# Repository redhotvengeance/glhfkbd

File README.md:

# glhfkbd

A custom, split keyboard.

Features:
- Extremely minimalist design -- no bevels, no edges, just keys!
- Split body, for da ergonomics
- Row-staggered, for da muscle memory
- A "Y" and "B" key on both halves, for da bad typists
- Supports hotswap MX sockets
- Fully embedded electronics -- no dev boards!
- USB-C for the wired interconnect -- no live TRRS shorts!
- Either side can act as the host
- Driven by QMK firmware and fully customizable

## PCB

The PCB is all one unit, despite both halves of the keyboard being asymmetrical. Mouse bites are used to easily separate pieces. All gerbers are provided in this repo.

All electronics are embedded into the board itself. This eliminates the need for a dev board, but requires assembly by a PCB manufacturer. BOM and position files are provided in this repo.

## Case

All pieces for the case are provided as STEP files in this repo, with the exception of the switch plates, which are provided as PCB files so they can be manufactored in FR4.

### Switch plates (required)

Found in the `pcb` folder. Should be printed as non-copper and non-trace PCBs.

### Filler layer (optional)

3D printed layer that sites between the plates and PCBs (to fill the space between switches). Used for aesthetics and sound.

### Standoff layer (required)

Used to mount the PCBs and plates to the base. Can be easily 3D printed. Needs heat-set inserts added.

### Base (required)

Bottom of the keyboard. Can be 3D printed. Should have rubber feet added for stability.

As an upgrade, the base can be laser cut from metal. This adds weight, quality, and improved sound. I suggest using a ferrous metal (like carbon steel) so that each keyboard half can be easily attached to a magsafe stand for easy tenting.

## Sharing

Fully open source. Feel free to build it yourself.

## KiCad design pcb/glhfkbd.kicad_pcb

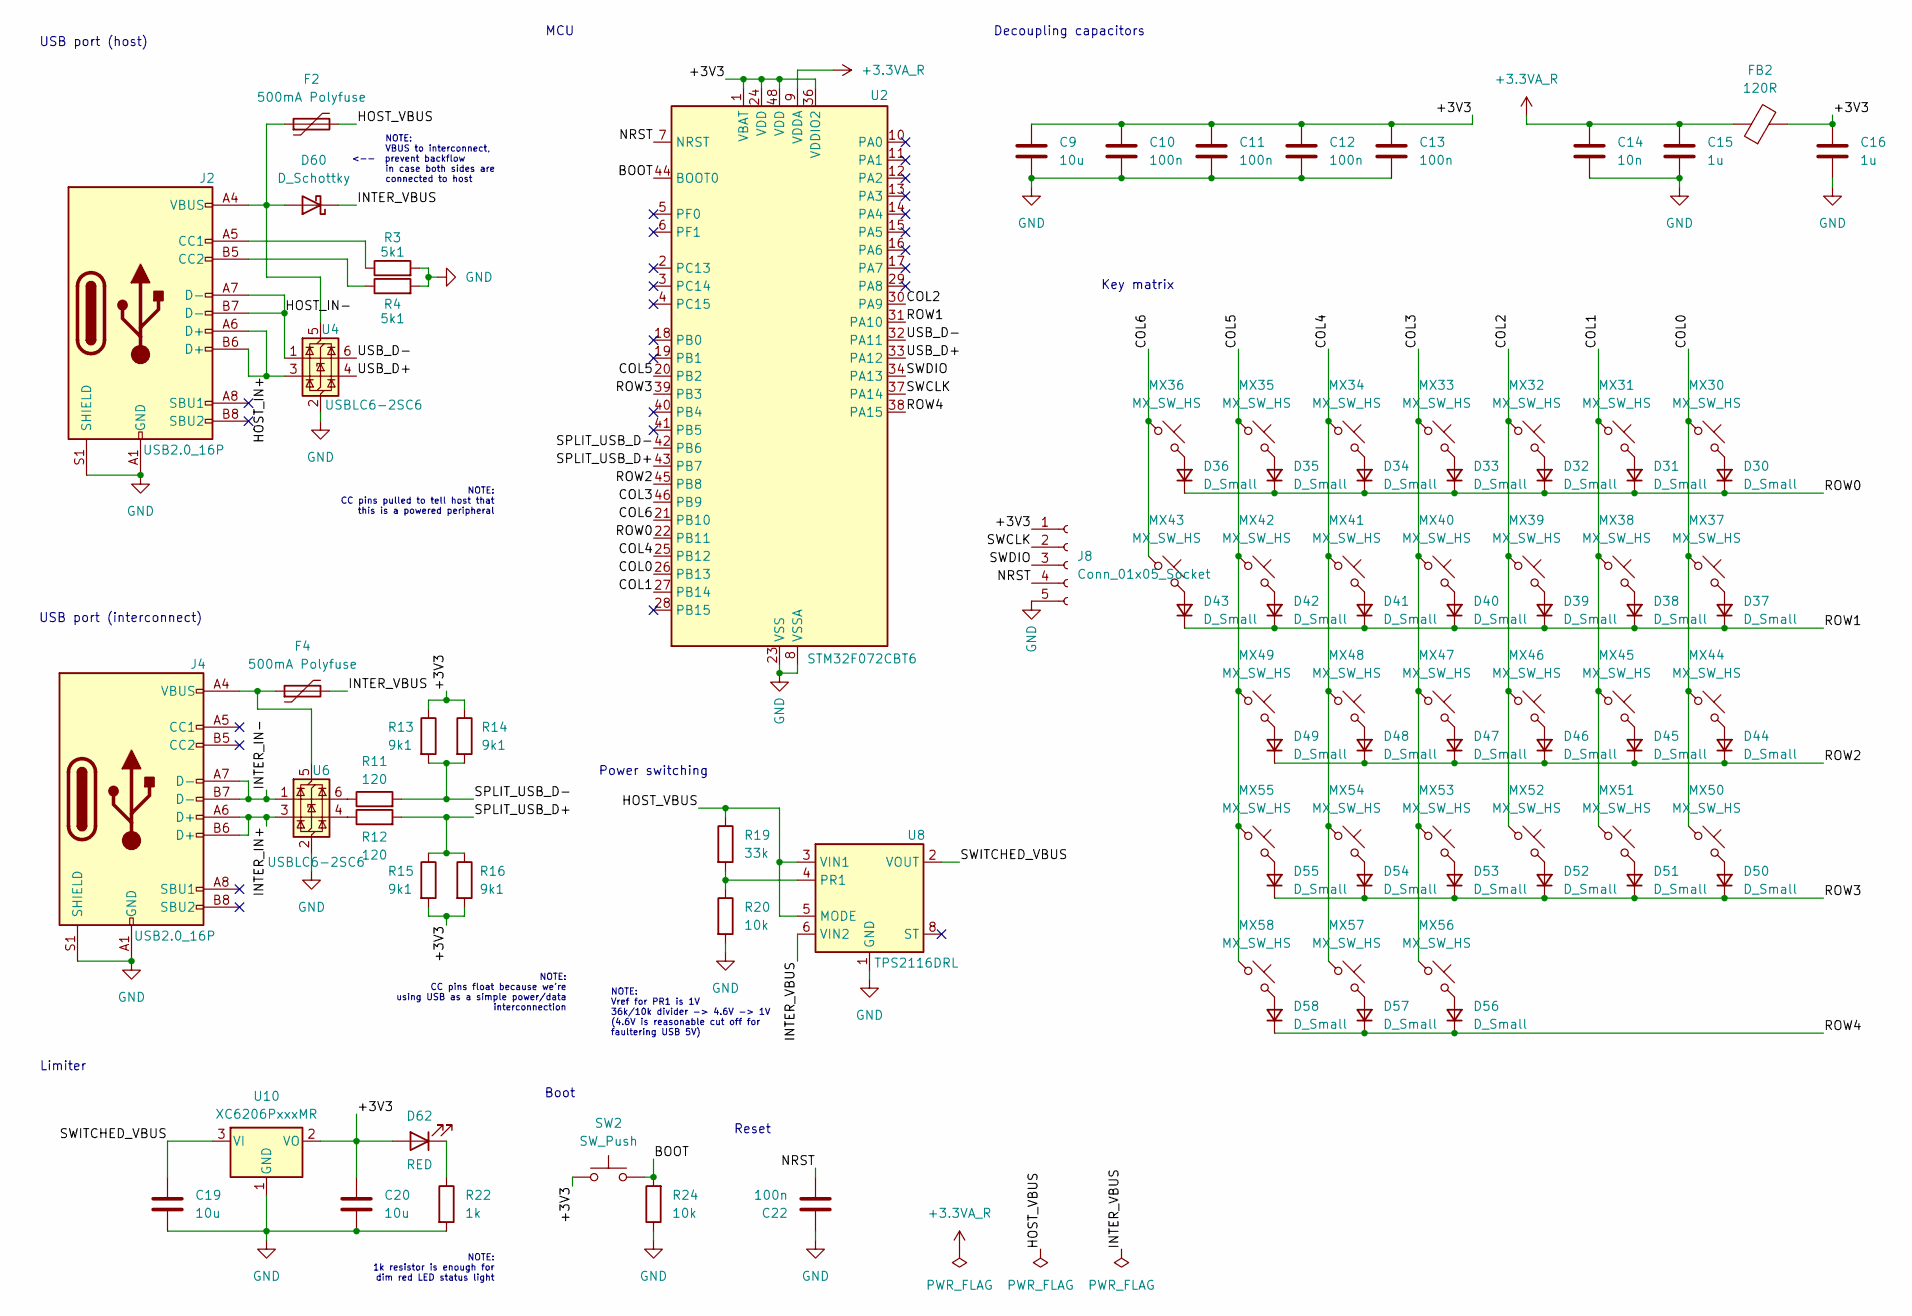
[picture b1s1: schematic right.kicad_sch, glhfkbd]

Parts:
C9, C19, C20: 10u; cap_10uf; Manufacturer Part CL05A106MQ5NUNC; LCSC C15525
C10, C11, C12, C13, C22: 100n; cap_100nf; Manufacturer Part CL05B104KB54PNC; LCSC C307331
C14: 10n; cap_10nf; Manufacturer Part CL05B103KB5NNNC; LCSC C15195
C15, C16: 1u; cap_1uf; Manufacturer Part CL05A105KA5NQNC; LCSC C52923
D30, D31, D32, D33, D34, D35, D36, D37, D38, D39, D40, D41, D42, D43, D44, D45, D46, D47, D48, D49, D50, D51, D52, D53, D54, D55, D56, D57, D58: D_Small; diode_sod123; Manufacturer Part 1N4148W; LCSC C81598
D60: D_Schottky; schottky; Manufacturer Part SS54; LCSC C22452
D62: RED; led; Manufacturer Part KT-0603R; LCSC C2286
F2, F4: 500mA Polyfuse; fuse_500ma; Manufacturer Part MF-FSMF050X-2; LCSC C210357
FB2: 120R; ferrite; Manufacturer Part BLM18SG260TN1D; LCSC C87063
J2, J4: USB2.0_16P; usb-c; Manufacturer Part TYPE-C-31-M-12; LCSC C165948
J8: Conn_01x05_Socket; PinHeader_1x05_P1.00mm_Vertical
MX30, MX31, MX32, MX33, MX34, MX35, MX36, MX37, MX38, MX39, MX40, MX41, MX42, MX43, MX44, MX45, MX46, MX47, MX48, MX49, MX50, MX51, MX52, MX53, MX54, MX55, MX56, MX57, MX58: MX_SW_HS; SW_MX_HS_CPG151101S11_1u
R3, R4: 5k1; res_5k1; Manufacturer Part 0402WGF5101TCE; LCSC C25905
R11, R12: 120; res_120; LCSC C25079
R13, R14, R15, R16: 9k1; res_9k1; LCSC C23260
R19: 33k; res_33k; Manufacturer Part 0402WGF3302TCE; LCSC C25779
R20, R24: 10k; res_10k; Manufacturer Part 0402WGF1002TCE; LCSC C25744
R22: 1k; res_1k; Manufacturer Part 0402WGF1001TCE; LCSC C11702
SW2: SW_Push; switch; Manufacturer Part TS-1088-AR02016; LCSC C720477
U2: STM32F072CBT6; stm32; Manufacturer Part STM32F072CBT6; LCSC C81720
U4, U6: USBLC6-2SC6; usblc6-2sc6; Manufacturer Part USBLC6-2SC6; LCSC C2827654
U8: TPS2116DRL; tps2116drlr; Manufacturer Part TPS2116DRLR; LCSC C3235557
U10: XC6206PxxxMR; xc6206; Manufacturer Part XC6206P332MR-G; LCSC C5446

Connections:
+3.3VA_R: C14.1, C15.1, FB2.1, U2.9 (VDDA)
/right/+3V3: C9.1, C10.1, C11.1, C12.1, C13.1, C16.1, C20.1, D62.2 (A), FB2.2, J8.1, R13.1, R14.1, R15.2, R16.2, SW2.1, U2.1 (VBAT), U2.24 (VDD), U2.36 (VDDIO2), U2.48 (VDD), U10.2 (VO)
/right/BOOT: R24.2, SW2.2, U2.44 (BOOT0)
/right/COL0: MX30.1, MX37.1, MX44.1, MX50.1, U2.26 (PB13)
/right/COL1: MX31.1, MX38.1, MX45.1, MX51.1, U2.27 (PB14)
/right/COL2: MX32.1, MX39.1, MX46.1, MX52.1, U2.30 (PA9)
/right/COL3: MX33.1, MX40.1, MX47.1, MX53.1, MX56.1, U2.46 (PB9)
/right/COL4: MX34.1, MX41.1, MX48.1, MX54.1, MX57.1, U2.25 (PB12)
/right/COL5: MX35.1, MX42.1, MX49.1, MX55.1, MX58.1, U2.20 (PB2)
/right/COL6: MX36.1, MX43.1, U2.21 (PB10)
/right/HOST_IN+: J2.A6 (D+), J2.B6 (D+), U4.3 (I/O2)
/right/HOST_IN-: J2.A7 (D-), J2.B7 (D-), U4.1 (I/O1)
/right/HOST_VBUS: F2.2, R19.1, U8.3 (VIN1), U8.5 (MODE)
/right/INTER_IN+: J4.A6 (D+), J4.B6 (D+), U6.3 (I/O2)
/right/INTER_IN-: J4.A7 (D-), J4.B7 (D-), U6.1 (I/O1)
/right/INTER_VBUS: D60.1 (K), F4.2, U8.6 (VIN2)
/right/NRST: C22.1, J8.4, U2.7 (NRST)
/right/ROW0: D30.1 (K), D31.1 (K), D32.1 (K), D33.1 (K), D34.1 (K), D35.1 (K), D36.1 (K), U2.22 (PB11)
/right/ROW1: D37.1 (K), D38.1 (K), D39.1 (K), D40.1 (K), D41.1 (K), D42.1 (K), D43.1 (K), U2.31 (PA10)
/right/ROW2: D44.1 (K), D45.1 (K), D46.1 (K), D47.1 (K), D48.1 (K), D49.1 (K), U2.45 (PB8)
/right/ROW3: D50.1 (K), D51.1 (K), D52.1 (K), D53.1 (K), D54.1 (K), D55.1 (K), U2.39 (PB3)
/right/ROW4: D56.1 (K), D57.1 (K), D58.1 (K), U2.38 (PA15)
/right/SPLIT_USB_D+: R12.2, R15.1, R16.1, U2.43 (PB7)
/right/SPLIT_USB_D-: R11.2, R13.2, R14.2, U2.42 (PB6)
/right/SWCLK: J8.2, U2.37 (PA14)
/right/SWDIO: J8.3, U2.34 (PA13)
/right/SWITCHED_VBUS: C19.1, U8.2 (VOUT), U8.7 (VOUT), U10.3 (VI)
/right/USB_D+: U2.33 (PA12), U4.4 (I/O2)
/right/USB_D-: U2.32 (PA11), U4.6 (I/O1)
GND: C9.2, C10.2, C11.2, C12.2, C13.2, C14.2, C15.2, C16.2, C19.2, C20.2, C22.2, J2.A1 (GND), J2.A12 (GND), J2.B1 (GND), J2.B12 (GND), J2.S1 (SHIELD), J4.A1 (GND), J4.A12 (GND), J4.B1 (GND), J4.B12 (GND), J4.S1 (SHIELD), J8.5, R3.2, R4.2, R20.2, R22.2, R24.1, U2.8 (VSSA), U2.23 (VSS), U2.35 (VSS), U2.47 (VSS), U4.2 (GND), U6.2 (GND), U8.1 (GND), U10.1 (GND); also elsewhere on the board
unnamed: D30.2 (A), MX30.2
unnamed: D31.2 (A), MX31.2
unnamed: D32.2 (A), MX32.2
unnamed: D33.2 (A), MX33.2
unnamed: D34.2 (A), MX34.2
unnamed: D35.2 (A), MX35.2
unnamed: D36.2 (A), MX36.2
unnamed: D37.2 (A), MX37.2
unnamed: D38.2 (A), MX38.2
unnamed: D39.2 (A), MX39.2
unnamed: D40.2 (A), MX40.2
unnamed: D41.2 (A), MX41.2
unnamed: D42.2 (A), MX42.2
unnamed: D43.2 (A), MX43.2
unnamed: D44.2 (A), MX44.2
unnamed: D45.2 (A), MX45.2
unnamed: D46.2 (A), MX46.2
unnamed: D47.2 (A), MX47.2
unnamed: D48.2 (A), MX48.2
unnamed: D49.2 (A), MX49.2
unnamed: D50.2 (A), MX50.2
unnamed: D51.2 (A), MX51.2
unnamed: D52.2 (A), MX52.2
unnamed: D53.2 (A), MX53.2
unnamed: D54.2 (A), MX54.2
unnamed: D55.2 (A), MX55.2
unnamed: D56.2 (A), MX56.2
unnamed: D57.2 (A), MX57.2
unnamed: D58.2 (A), MX58.2
unnamed: D60.2 (A), F2.1, J2.A4 (VBUS), J2.A9 (VBUS), J2.B4 (VBUS), J2.B9 (VBUS), U4.5 (VBUS)
unnamed: D62.1 (K), R22.1
unnamed: J2.A5 (CC1), R3.1
unnamed: J2.B5 (CC2), R4.1
unnamed: R11.1, U6.6 (I/O1)
unnamed: R12.1, U6.4 (I/O2)
unnamed: F4.1, J4.A4 (VBUS), J4.A9 (VBUS), J4.B4 (VBUS), J4.B9 (VBUS), U6.5 (VBUS)
unnamed: R19.2, R20.1, U8.4 (PR1)

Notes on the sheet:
USB port (interconnect)
NOTE: CC pins float because we're using USB as a simple power/data interconnection
Power switching
USB port (host)
Decoupling capacitors
NOTE: VBUS to interconnect, <-- prevent backflow in case both sides are connected to host
Key matrix
NOTE: 1k resistor is enough for dim red LED status light
NOTE: Vref for PR1 is 1V 36k/10k divider -> 4.6V -> 1V (4.6V is reasonable cut off for faultering USB 5V)
Reset
NOTE: CC pins pulled to tell host that this is a powered peripheral
Limiter
MCU
Boot

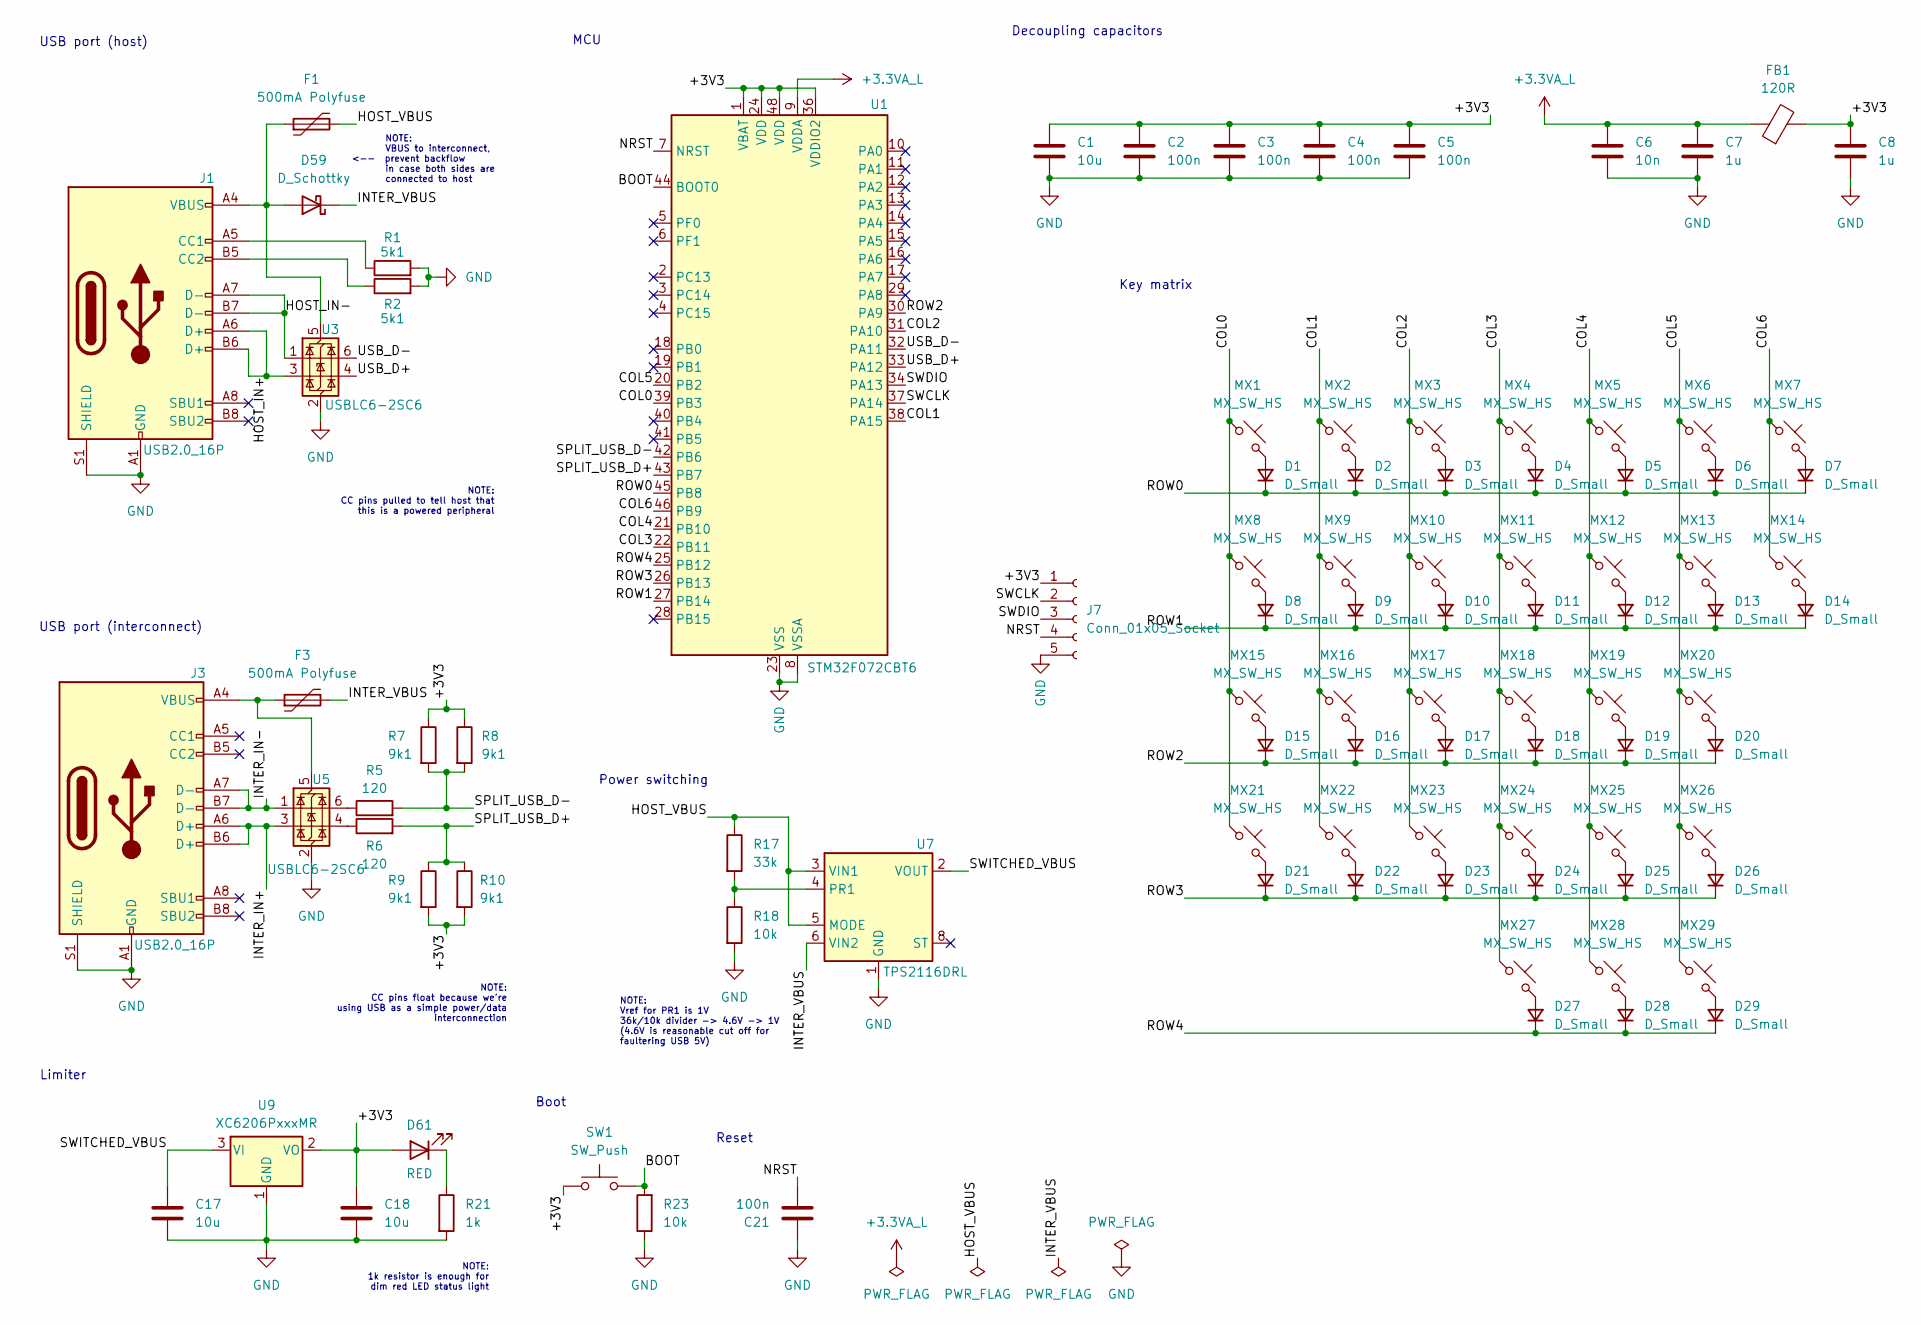
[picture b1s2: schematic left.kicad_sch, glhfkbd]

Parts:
C1, C17, C18: 10u; cap_10uf; Manufacturer Part CL05A106MQ5NUNC; LCSC C15525
C2, C3, C4, C5, C21: 100n; cap_100nf; Manufacturer Part CL05B104KB54PNC; LCSC C307331
C6: 10n; cap_10nf; Manufacturer Part CL05B103KB5NNNC; LCSC C15195
C7, C8: 1u; cap_1uf; Manufacturer Part CL05A105KA5NQNC; LCSC C52923
D1, D2, D3, D4, D5, D6, D7, D8, D9, D10, D11, D12, D13, D14, D15, D16, D17, D18, D19, D20, D21, D22, D23, D24, D25, D26, D27, D28, D29: D_Small; diode_sod123; Manufacturer Part 1N4148W; LCSC C81598
D59: D_Schottky; schottky; Manufacturer Part SS54; LCSC C22452
D61: RED; led; Manufacturer Part KT-0603R; LCSC C2286
F1, F3: 500mA Polyfuse; fuse_500ma; Manufacturer Part MF-FSMF050X-2; LCSC C210357
FB1: 120R; ferrite; Manufacturer Part BLM18SG260TN1D; LCSC C87063
J1, J3: USB2.0_16P; usb-c; Manufacturer Part TYPE-C-31-M-12; LCSC C165948
J7: Conn_01x05_Socket; PinHeader_1x05_P1.00mm_Vertical
MX1, MX2, MX3, MX4, MX5, MX6, MX7, MX8, MX9, MX10, MX11, MX12, MX13, MX14, MX15, MX16, MX17, MX18, MX19, MX20, MX21, MX22, MX23, MX24, MX25, MX26, MX27, MX28, MX29: MX_SW_HS; SW_MX_HS_CPG151101S11_1u
R1, R2: 5k1; res_5k1; Manufacturer Part 0402WGF5101TCE; LCSC C25905
R5, R6: 120; res_120; LCSC C25079
R7, R8, R9, R10: 9k1; res_9k1; LCSC C23260
R17: 33k; res_33k; Manufacturer Part 0402WGF3302TCE; LCSC C25779
R18, R23: 10k; res_10k; Manufacturer Part 0402WGF1002TCE; LCSC C25744
R21: 1k; res_1k; Manufacturer Part 0402WGF1001TCE; LCSC C11702
SW1: SW_Push; switch; Manufacturer Part TS-1088-AR02016; LCSC C720477
U1: STM32F072CBT6; stm32; Manufacturer Part STM32F072CBT6; LCSC C81720
U3, U5: USBLC6-2SC6; usblc6-2sc6; Manufacturer Part USBLC6-2SC6; LCSC C2827654
U7: TPS2116DRL; tps2116drlr; Manufacturer Part TPS2116DRLR; LCSC C3235557
U9: XC6206PxxxMR; xc6206; Manufacturer Part XC6206P332MR-G; LCSC C5446

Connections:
+3.3VA_L: C6.1, C7.1, FB1.1, U1.9 (VDDA)
/left/+3V3: C1.1, C2.1, C3.1, C4.1, C5.1, C8.1, C18.1, D61.2 (A), FB1.2, J7.1, R7.1, R8.1, R9.2, R10.2, SW1.1, U1.1 (VBAT), U1.24 (VDD), U1.36 (VDDIO2), U1.48 (VDD), U9.2 (VO)
/left/BOOT: R23.2, SW1.2, U1.44 (BOOT0)
/left/COL0: MX1.1, MX8.1, MX15.1, MX21.1, U1.39 (PB3)
/left/COL1: MX2.1, MX9.1, MX16.1, MX22.1, U1.38 (PA15)
/left/COL2: MX3.1, MX10.1, MX17.1, MX23.1, U1.31 (PA10)
/left/COL3: MX4.1, MX11.1, MX18.1, MX24.1, MX27.1, U1.22 (PB11)
/left/COL4: MX5.1, MX12.1, MX19.1, MX25.1, MX28.1, U1.21 (PB10)
/left/COL5: MX6.1, MX13.1, MX20.1, MX26.1, MX29.1, U1.20 (PB2)
/left/COL6: MX7.1, MX14.1, U1.46 (PB9)
/left/HOST_IN+: J1.A6 (D+), J1.B6 (D+), U3.3 (I/O2)
/left/HOST_IN-: J1.A7 (D-), J1.B7 (D-), U3.1 (I/O1)
/left/HOST_VBUS: F1.2, R17.1, U7.3 (VIN1), U7.5 (MODE)
/left/INTER_IN+: J3.A6 (D+), J3.B6 (D+), U5.3 (I/O2)
/left/INTER_IN-: J3.A7 (D-), J3.B7 (D-), U5.1 (I/O1)
/left/INTER_VBUS: D59.1 (K), F3.2, U7.6 (VIN2)
/left/NRST: C21.1, J7.4, U1.7 (NRST)
/left/ROW0: D1.1 (K), D2.1 (K), D3.1 (K), D4.1 (K), D5.1 (K), D6.1 (K), D7.1 (K), U1.45 (PB8)
/left/ROW1: D8.1 (K), D9.1 (K), D10.1 (K), D11.1 (K), D12.1 (K), D13.1 (K), D14.1 (K), U1.27 (PB14)
/left/ROW2: D15.1 (K), D16.1 (K), D17.1 (K), D18.1 (K), D19.1 (K), D20.1 (K), U1.30 (PA9)
/left/ROW3: D21.1 (K), D22.1 (K), D23.1 (K), D24.1 (K), D25.1 (K), D26.1 (K), U1.26 (PB13)
/left/ROW4: D27.1 (K), D28.1 (K), D29.1 (K), U1.25 (PB12)
/left/SPLIT_USB_D+: R6.2, R9.1, R10.1, U1.43 (PB7)
/left/SPLIT_USB_D-: R5.2, R7.2, R8.2, U1.42 (PB6)
/left/SWCLK: J7.2, U1.37 (PA14)
/left/SWDIO: J7.3, U1.34 (PA13)
/left/SWITCHED_VBUS: C17.1, U7.2 (VOUT), U7.7 (VOUT), U9.3 (VI)
/left/USB_D+: U1.33 (PA12), U3.4 (I/O2)
/left/USB_D-: U1.32 (PA11), U3.6 (I/O1)
GND: C1.2, C2.2, C3.2, C4.2, C5.2, C6.2, C7.2, C8.2, C17.2, C18.2, C21.2, J1.A1 (GND), J1.A12 (GND), J1.B1 (GND), J1.B12 (GND), J1.S1 (SHIELD), J3.A1 (GND), J3.A12 (GND), J3.B1 (GND), J3.B12 (GND), J3.S1 (SHIELD), J7.5, R1.2, R2.2, R18.2, R21.2, R23.1, U1.8 (VSSA), U1.23 (VSS), U1.35 (VSS), U1.47 (VSS), U3.2 (GND), U5.2 (GND), U7.1 (GND), U9.1 (GND); also elsewhere on the board
unnamed: D1.2 (A), MX1.2
unnamed: D2.2 (A), MX2.2
unnamed: D3.2 (A), MX3.2
unnamed: D4.2 (A), MX4.2
unnamed: D5.2 (A), MX5.2
unnamed: D6.2 (A), MX6.2
unnamed: D7.2 (A), MX7.2
unnamed: D8.2 (A), MX8.2
unnamed: D9.2 (A), MX9.2
unnamed: D10.2 (A), MX10.2
unnamed: D11.2 (A), MX11.2
unnamed: D12.2 (A), MX12.2
unnamed: D13.2 (A), MX13.2
unnamed: D14.2 (A), MX14.2
unnamed: D15.2 (A), MX15.2
unnamed: D16.2 (A), MX16.2
unnamed: D17.2 (A), MX17.2
unnamed: D18.2 (A), MX18.2
unnamed: D19.2 (A), MX19.2
unnamed: D20.2 (A), MX20.2
unnamed: D21.2 (A), MX21.2
unnamed: D22.2 (A), MX22.2
unnamed: D23.2 (A), MX23.2
unnamed: D24.2 (A), MX24.2
unnamed: D25.2 (A), MX25.2
unnamed: D26.2 (A), MX26.2
unnamed: D27.2 (A), MX27.2
unnamed: D28.2 (A), MX28.2
unnamed: D29.2 (A), MX29.2
unnamed: D59.2 (A), F1.1, J1.A4 (VBUS), J1.A9 (VBUS), J1.B4 (VBUS), J1.B9 (VBUS), U3.5 (VBUS)
unnamed: D61.1 (K), R21.1
unnamed: J1.A5 (CC1), R1.1
unnamed: J1.B5 (CC2), R2.1
unnamed: R5.1, U5.6 (I/O1)
unnamed: R6.1, U5.4 (I/O2)
unnamed: F3.1, J3.A4 (VBUS), J3.A9 (VBUS), J3.B4 (VBUS), J3.B9 (VBUS), U5.5 (VBUS)
unnamed: R17.2, R18.1, U7.4 (PR1)

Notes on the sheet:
NOTE: CC pins float because we're using USB as a simple power/data interconnection
Power switching
NOTE: CC pins pulled to tell host that this is a powered peripheral
NOTE: 1k resistor is enough for dim red LED status light
Decoupling capacitors
USB port (host)
Reset
NOTE: VBUS to interconnect, <-- prevent backflow in case both sides are connected to host
NOTE: Vref for PR1 is 1V 36k/10k divider -> 4.6V -> 1V (4.6V is reasonable cut off for faultering USB 5V)
Key matrix
USB port (interconnect)
Boot
MCU
Limiter

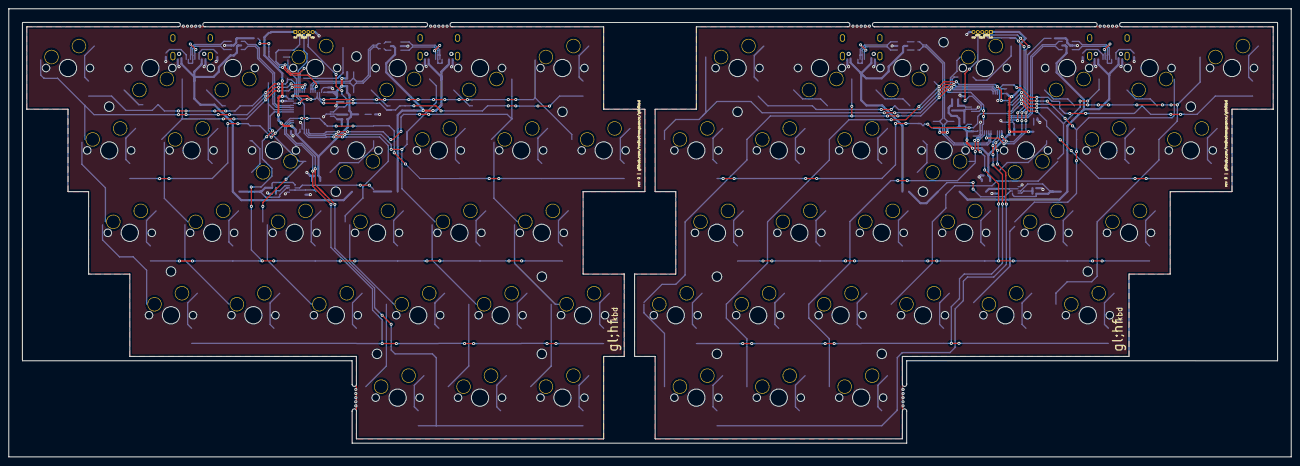
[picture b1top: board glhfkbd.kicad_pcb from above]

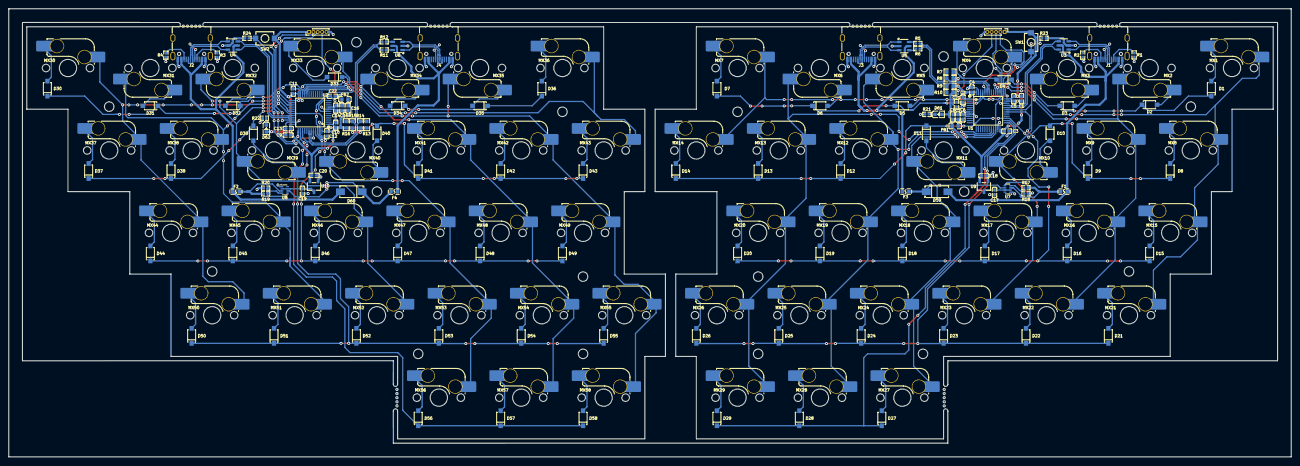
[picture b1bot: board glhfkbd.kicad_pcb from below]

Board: 2 copper layers, 296.5 x 103.6 mm, 206 parts (191 on the bottom side), 133 nets.

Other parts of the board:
M2, M2#2, M2#3, M2#4, M2#5, M2#6, M2#7, M2#8, M2#9, M2#10, M2#11, M2#12, M2#13, M2#14, M2#15, M2#16: MountingHole_2.2mm_M2

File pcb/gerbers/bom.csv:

Designator,Footprint,Quantity,Value,LCSC Part #
"C1, C17, C18, C19, C20, C9",cap_10uf,6,10u,C15525
"C10, C11, C12, C13, C2, C21, C22, C3, C4, C5",cap_100nf,10,100n,C307331
"C14, C6",cap_10nf,2,10n,C15195
"C15, C16, C7, C8",cap_1uf,4,1u,C52923
"D1, D10, D11, D12, D13, D14, D15, D16, D17, D18, D19, D2, D20, D21, D22, D23, D24, D25, D26, D27, D28, D29, D3, D30, D31, D32, D33, D34, D35, D36, D37, D38, D39, D4, D40, D41, D42, D43, D44, D45, D46, D47, D48, D49, D5, D50, D51, D52, D53, D54, D55, D56, D57, D58, D6, D7, D8, D9",diode_sod123,58,D_Small,C81598
"D59, D60",schottky,2,D_Schottky,C22452
"D61, D62",led,2,RED,C2286
"F1, F2, F3, F4",fuse_500ma,4,500mA Polyfuse,C210357
"FB1, FB2",ferrite,2,120R,C87063
"J1, J2, J3, J4",usb-c,4,USB2.0_16P,C165948
"R1, R2, R3, R4",res_5k1,4,5k1,C25905
"R10, R13, R14, R15, R16, R7, R8, R9",res_9k1,8,9k1,C23260
"R11, R12, R5, R6",res_120,4,120,C25079
"R17, R19",res_33k,2,33k,C25779
"R18, R20, R23, R24",res_10k,4,10k,C25744
"R21, R22",res_1k,2,1k,C11702
"SW1, SW2",switch,2,SW_Push,C720477
"U1, U2",stm32,2,STM32F072CBT6,C81720
"U10, U9",xc6206,2,XC6206PxxxMR,C5446
"U3, U4, U5, U6",usblc6-2sc6,4,USBLC6-2SC6,C2827654
"U7, U8",tps2116drlr,2,TPS2116DRL,C3235557

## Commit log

2025-11-24 Add flake.nix
2025-11-24 Add pcb
2025-11-24 Add case
2025-11-24 Add gerbers
2025-12-09 Add step files
